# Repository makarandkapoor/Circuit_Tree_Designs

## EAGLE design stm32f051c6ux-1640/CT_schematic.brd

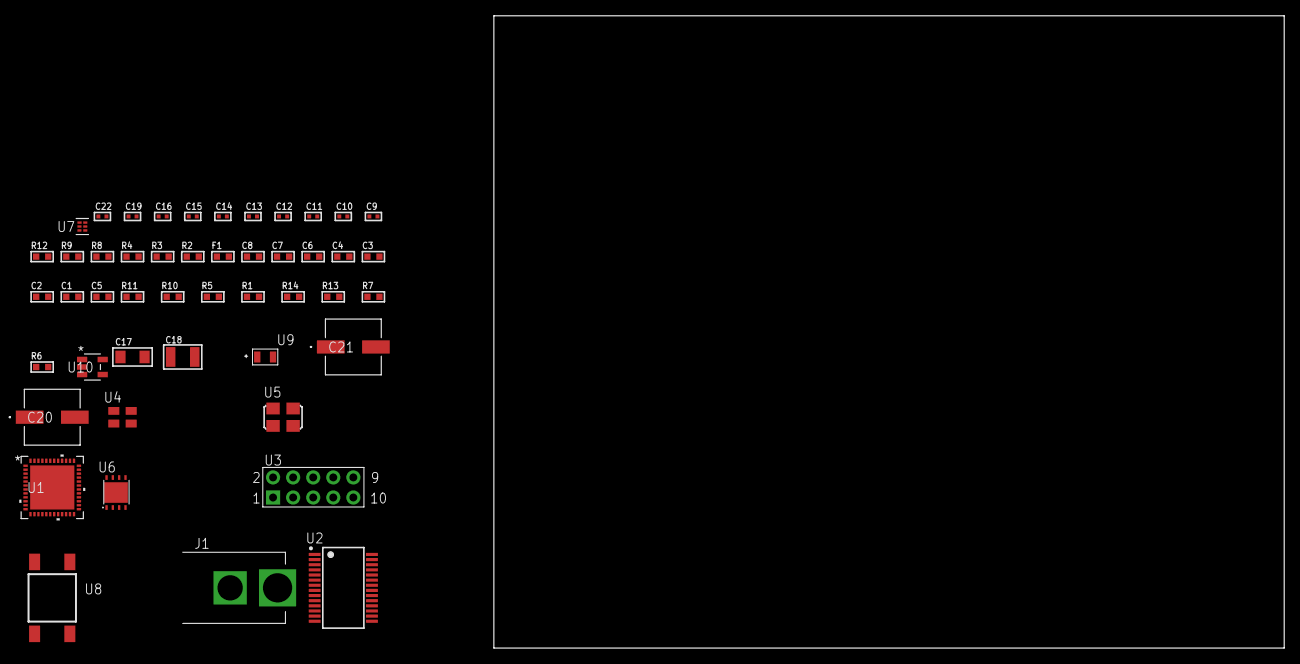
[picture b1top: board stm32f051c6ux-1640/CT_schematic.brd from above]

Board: 2 copper layers, 100.0 x 80.0 mm, 48 parts (0 on the bottom side), 32 nets, no tracks yet.

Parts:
C1, C8: 1e-06; C0603
C2, C3, C4, C6: 1e-07; C0603
C5: 4.7e-06; C0603
C7: 1e-08; C0603
C9, C10, C11, C12, C13, C19: 1e-07; C0402
C14, C15, C16, C22: 1e-08; C0402
C17: 1e-05; C1206
C18: 1e-05; C1210
C20, C21: 0.0001; EXV-9H
F1: 240.0; L0603
J1: PJ-037B; PJ-037B_PACKAGE
R1, R5, R10, R11: 10000.0; R0603
R2, R9: 1000.0; R0603
R3: 1600.5; R0603
R4: 4700.0; R0603
R6, R7: 100000.0; R0603
R8: 2231.0; R0603
R12: 9100.0; R0603
R13: 680000.0; R0603
R14: 120000.0; R0603
U1: stm32f051c6u6; UFQFPN48
U2: ST3241EBPR; SSOP-28
U3: HTSS-105-01-G-D
U4: ASEK-32.768KHz-ECST; ASEK
U5: ASFL1-25MHZ-NCS; ASFL1
U6: LP3878SDX-ADJ/NOPB; WSON-8
U7: TPS3895ADRYR; SON-6
U8: 4-1437565-2; SW_4-1437565-2
U9: Q65110A2395; LGM67K-G1J2-24-Z
U10: nc7sz125m5x; NC7SZ125M5X

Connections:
CLK_U1_3: U1.3, U4.3
CLK_U1_5: U1.5, U5.3
GND: C1.2, C2.2, C3.2, C4.2, C5.2, C6.2, C7.2, C8.2, C9.2, C12.2, C13.2, C14.2, C15.2, C16.2, C17.2, C18.2, C19.2, C20.2, C21.2, C22.2, J1.2, R2.2, R5.2, R9.2, R12.2, R14.2, U1.8, U1.23, U1.47, U1.49, U2.23, U2.25, U3.9, U4.2, U5.2, U6.3, U6.PAD, U7.2, U9.C, U10.1, U10.3
NET_U1_7: R4.1, U1.7, U10.4
NET_U1_9: C7.1, C8.1, F1.1, U1.9
NET_U1_44: R5.1, U1.44
NET_U1_45: R3.1, U1.45, U9.A
NET_U1_46: R1.1, U1.46, U8.3, U8.4
NET_U2_1: C11.1, U2.1
NET_U2_2: C11.2, U2.2
NET_U2_3: C13.1, U2.3
NET_U2_22: R6.1, U2.22
NET_U2_24: C10.2, U2.24
NET_U2_27: C12.1, U2.27
NET_U2_28: C10.1, U2.28
NET_U3_3: U2.4, U3.3
NET_U3_4: U2.5, U3.4
NET_U3_5: U2.9, U3.5
NET_U3_6: U2.10, U3.6
NET_U6_1: C16.1, U6.1
NET_U6_6: R8.2, R9.1, U6.6
NET_U6_8: R7.1, U6.8
NET_U7_1: R11.1, R12.1, U7.1
NET_U7_3: R13.2, R14.1, U7.3
NET_U7_4: R10.1, U7.4, U10.2
NET_U8_1: R2.1, U8.1, U8.2
PROC_USART1_CTS: U1.32, U2.13
PROC_USART1_RTS: U1.33, U2.18
PROC_USART1_RX: U1.31, U2.19
PROC_USART1_TX: U1.30, U2.14
VCC_S1_7V3: C17.1, C20.1, C21.1, J1.1, R7.2, U6.4
VCC_TIER1_3V3: C1.1, C2.1, C3.1, C4.1, C5.1, C6.1, C9.1, C14.1, C15.1, C18.1, C19.1, C22.1, F1.2, R1.2, R3.2, R4.2, R6.2, R8.1, R10.2, R11.2, R13.1, U1.1, U1.24, U1.48, U2.26, U4.4, U5.4, U6.5, U7.6, U10.5

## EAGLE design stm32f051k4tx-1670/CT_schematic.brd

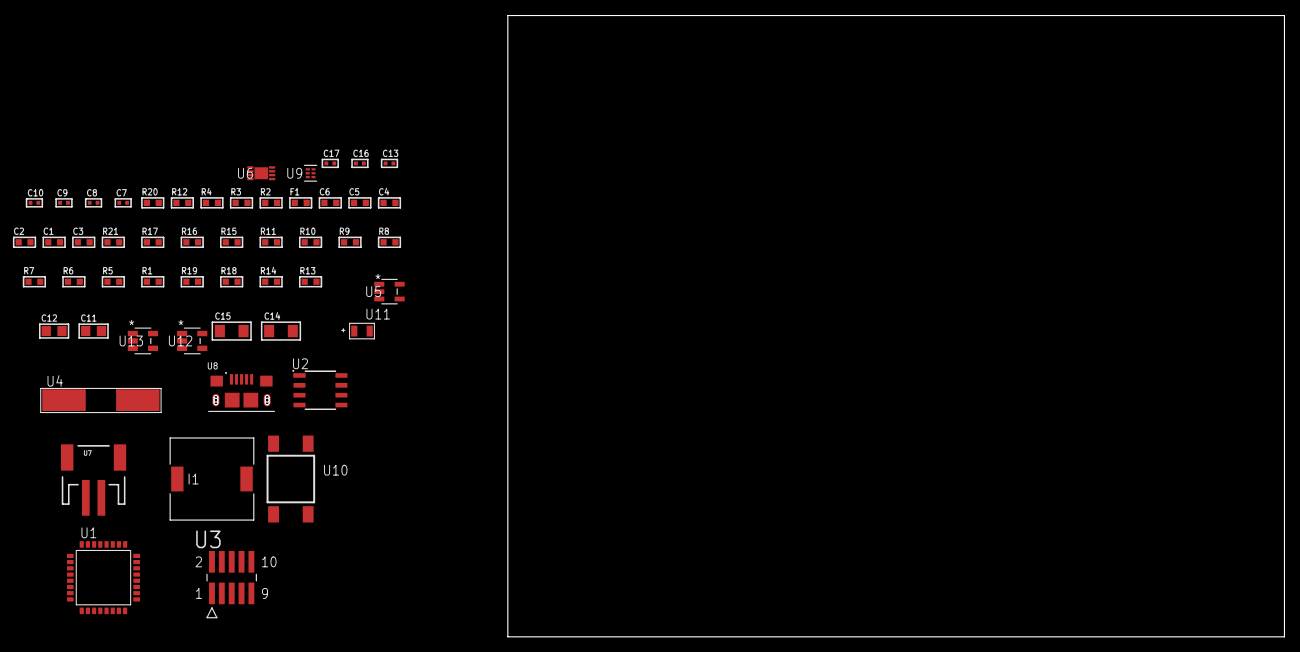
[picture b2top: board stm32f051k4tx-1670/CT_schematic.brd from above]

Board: 2 copper layers, 53 parts (0 on the bottom side), 30 nets, no tracks yet.

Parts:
C1, C2: 1e-07; C0603
C3: 4.7e-06; C0603
C4, C5: 1e-08; C0603
C6: 1e-06; C0603
C7, C8: 1e-11; C0402
C9, C16, C17: 1e-08; C0402
C10, C13: 1e-07; C0402
C11, C12: 1e-05; C0805
C14, C15: 1e-05; C1206
F1: 240.0; L0603
I1: 7e-06; DR1040
R1, R5, R6, R7, R8, R9, R10, R11, R15, R16, R21: 10000.0; R0603
R2: 1000.0; R0603
R3: 1270.0; R0603
R4: 4700.0; R0603
R12: 5.0; R0603
R13: 309473.68421053; R0603
R14: 1000000.0; R0603
R17: 18000.0; R0603
R18: 470000.0; R0603
R19: 120000.0; R0603
R20: 2000.0; R0603
U1: stm32f051k4t7; LQFP32
U2: AT25010B-SSHL-T; SOIC-8
U3: FTSH-105-01-L-DV-K; SAMTEC_FTSH-105-01-L-DV-K
U4: ABLS-25.000MHZ-B2F-T
U5: ltc3406es5; TSOT-23-5
U6: MCP73831T-2ACI/MC; DFN8_2X3MC
U7: S2B-PH-SM4-TB(LF)(SN); JST-2-SMD
U8: 10118193-0001LF; FCI_10118193-0001LF
U9: TPS3895ADRYR; SON-6
U10: 4-1437565-2; SW_4-1437565-2
U11: Q65110A2395; LGM67K-G1J2-24-Z
U12, U13: nc7sz125m5x; NC7SZ125M5X

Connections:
CLK_CRYSTAL_U1_2: C7.1, U1.2, U4.1
CLK_CRYSTAL_U1_3: C8.1, U1.3, U4.2
GND: C1.2, C2.2, C3.2, C4.2, C5.2, C6.2, C7.2, C8.2, C9.2, C10.2, C11.2, C12.1, C12.2, C13.2, C14.2, C15.2, C16.2, C17.2, R2.2, R5.2, R12.2, R13.2, R17.2, R19.2, R20.2, U1.16, U1.32, U2.4, U3.3, U3.5, U5.2, U6.6, U6.9, U7.2, U8.5, U8.6, U8.7, U8.8, U8.9, U9.2, U11.C, U12.2, U12.3, U13.1, U13.3
INPUT_USBPOWER_5V: C14.1, R21.2, U6.1, U6.2, U8.1
NET_U1_4: R4.1, U1.4, U13.4
NET_U1_5: C4.1, C5.1, C6.1, F1.1, U1.5
NET_U1_29: R3.1, U1.29, U11.A
NET_U1_30: R1.1, U1.30, U10.3, U10.4
NET_U1_31: R5.1, U1.31
NET_U2_3: R6.1, U2.3
NET_U2_7: R8.1, U2.7
NET_U3_4: R10.1, U3.4
NET_U3_9: R12.1, U3.9
NET_U5_3: I1.1, U5.3
NET_U5_5: R13.1, R14.1, U5.5
NET_U5_ATNET_3: I1.2, R14.2
NET_U6_5: R21.1, U6.5
NET_U6_8: R20.1, U6.8
NET_U9_1: R16.1, R17.1, U9.1
NET_U9_3: R18.2, R19.1, U9.3
NET_U9_4: R15.1, U9.4, U12.4, U13.2
NET_U10_1: R2.1, U10.1, U10.2
PROC_SPI1_MISO: U1.12, U2.2
PROC_SPI1_MOSI: U1.13, U2.5
PROC_SPI1_NSS: R7.1, U1.10, U2.1
PROC_SPI1_SCK: U1.11, U2.6
PROC_SYS_SWDIO: R11.1, U1.23, U3.2
RST_OUT_U3_JTAG_RST_B: R9.1, U3.10, U12.1
VCC_S1_3V7: C11.1, C15.1, U5.4, U6.3, U6.4, U7.1
VCC_TIER1_2V5: C1.1, C2.1, C3.1, C9.1, C10.1, C12.2, C13.1, C16.1, C17.1, F1.2, I1.2, R1.2, R3.2, R4.2, R6.2, R7.2, R8.2, R9.2, R10.2, R11.2, R14.2, R15.2, R16.2, R18.1, U1.1, U1.17, U2.8, U3.1, U9.6, U12.5, U13.5

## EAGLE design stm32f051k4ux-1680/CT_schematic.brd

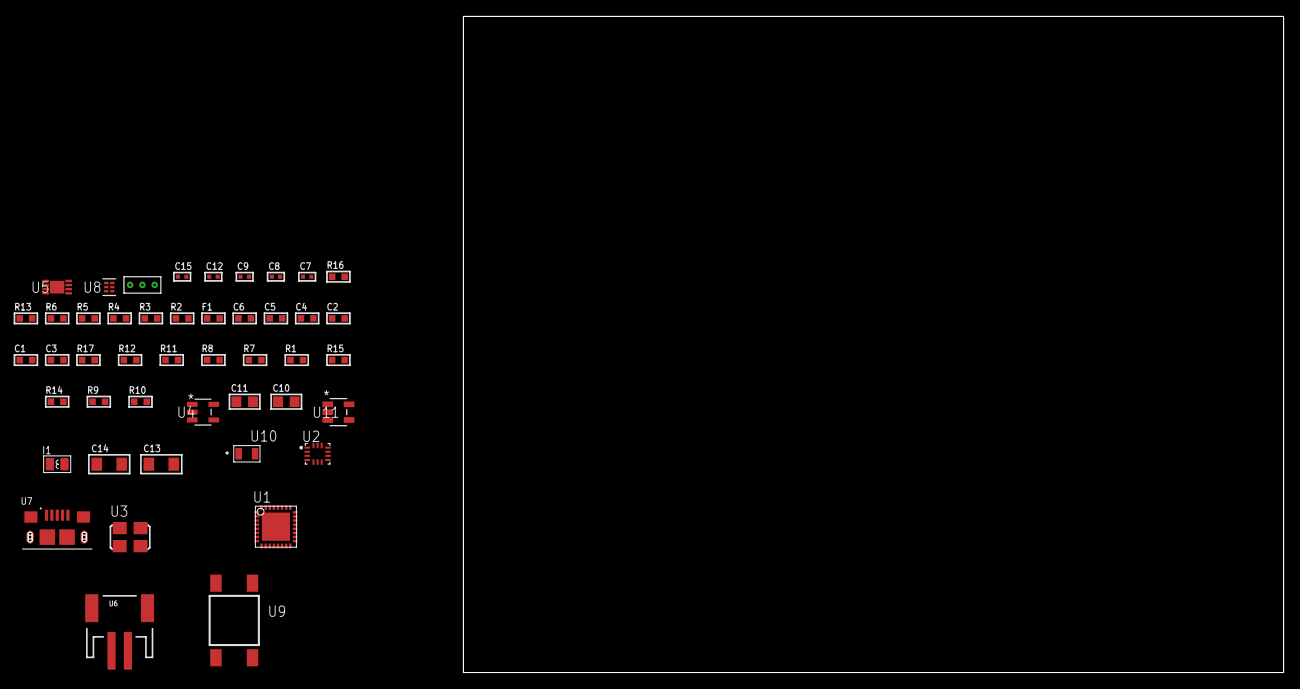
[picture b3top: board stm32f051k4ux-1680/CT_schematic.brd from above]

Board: 2 copper layers, 153.1 x 80.0 mm, 46 parts (0 on the bottom side), 25 nets, no tracks yet.

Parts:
C1, C2: 1e-07; C0603
C3: 4.7e-06; C0603
C4, C5: 1e-08; C0603
C6: 1e-06; C0603
C7, C8, C12: 1e-07; C0402
C9, C15: 1e-08; C0402
C10, C11: 1e-05; C0805
C13, C14: 1e-05; C1206
F1: 240.0; L0603
I1: 3.3e-06; L0806
R1, R7, R8, R11, R12, R17: 10000.0; R0603
R2: 1000.0; R0603
R3: 1600.5; R0603
R4: 4700.0; R0603
R5, R6: 2200.0; R0603
R9: 220000.0; R0603
R10: 1000000.0; R0603
R13: 9100.0; R0603
R14: 680000.0; R0603
R15: 120000.0; R0603
R16: 2000.0; R0603
U1: stm32f051k4u7; UFQFPN32
U2: BMG250; LGA-14
U3: ASFL1-25MHZ-NCS; ASFL1
U4: ltc3406es5; TSOT-23-5
U5: MCP73831T-2ACI/MC; DFN8_2X3MC
U6: S2B-PH-SM4-TB(LF)(SN); JST-2-SMD
U7: 10118193-0001LF; FCI_10118193-0001LF
U8: TPS3895ADRYR; SON-6
U9: 4-1437565-2; SW_4-1437565-2
U10: Q65110A2395; LGM67K-G1J2-24-Z
U11: nc7sz125m5x; NC7SZ125M5X
U12: Dummy; DUMMY_PACKAGE_99

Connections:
CLK_U1_2: U1.2, U3.3
GND: C1.2, C2.2, C3.2, C4.2, C5.2, C6.2, C7.2, C8.2, C9.2, C10.2, C11.1, C11.2, C12.2, C13.2, C14.2, C15.2, R2.2, R7.2, R9.2, R13.2, R15.2, R16.2, U1.EPAD, U2.1, U2.6, U2.7, U3.2, U4.2, U5.6, U5.9, U6.2, U7.5, U7.6, U7.7, U7.8, U7.9, U8.2, U10.C, U11.1, U11.3, U12.1
INPUT_USBPOWER_5V: C13.1, R17.2, U5.1, U5.2, U7.1
NET_U1_4: R4.1, U1.4, U11.4
NET_U1_5: C4.1, C5.1, C6.1, F1.1, U1.5
NET_U1_28: R3.1, U1.28, U10.A
NET_U1_29: R5.1, U1.29, U2.13
NET_U1_30: R6.1, U1.30, U2.14
NET_U1_31: R7.1, U1.31
NET_U1_32: R1.1, U1.32, U9.3, U9.4
NET_U2_12: R8.1, U2.12
NET_U4_3: I1.1, U4.3
NET_U4_5: R9.1, R10.1, U4.5
NET_U4_ATNET_3: I1.2, R10.2
NET_U5_5: R17.1, U5.5
NET_U5_8: R16.1, U5.8
NET_U8_1: R12.1, R13.1, U8.1
NET_U8_3: R14.2, R15.1, U8.3
NET_U8_4: R11.1, U8.4, U11.2
NET_U9_1: R2.1, U9.1, U9.2
PROC_GPIO_TO_U2_INT1: U1.3, U2.4
PROC_PA0: U1.6, U12.2
PROC_PA1: U1.7, U12.3
VCC_S1_3V7: C10.1, C14.1, U4.4, U5.3, U5.4, U6.1
VCC_TIER1_3V3: C1.1, C2.1, C3.1, C7.1, C8.1, C9.1, C11.2, C12.1, C15.1, F1.2, I1.2, R1.2, R3.2, R4.2, R5.2, R6.2, R8.2, R10.2, R11.2, R12.2, R14.1, U1.1, U1.17, U2.5, U2.8, U3.4, U8.6, U11.5

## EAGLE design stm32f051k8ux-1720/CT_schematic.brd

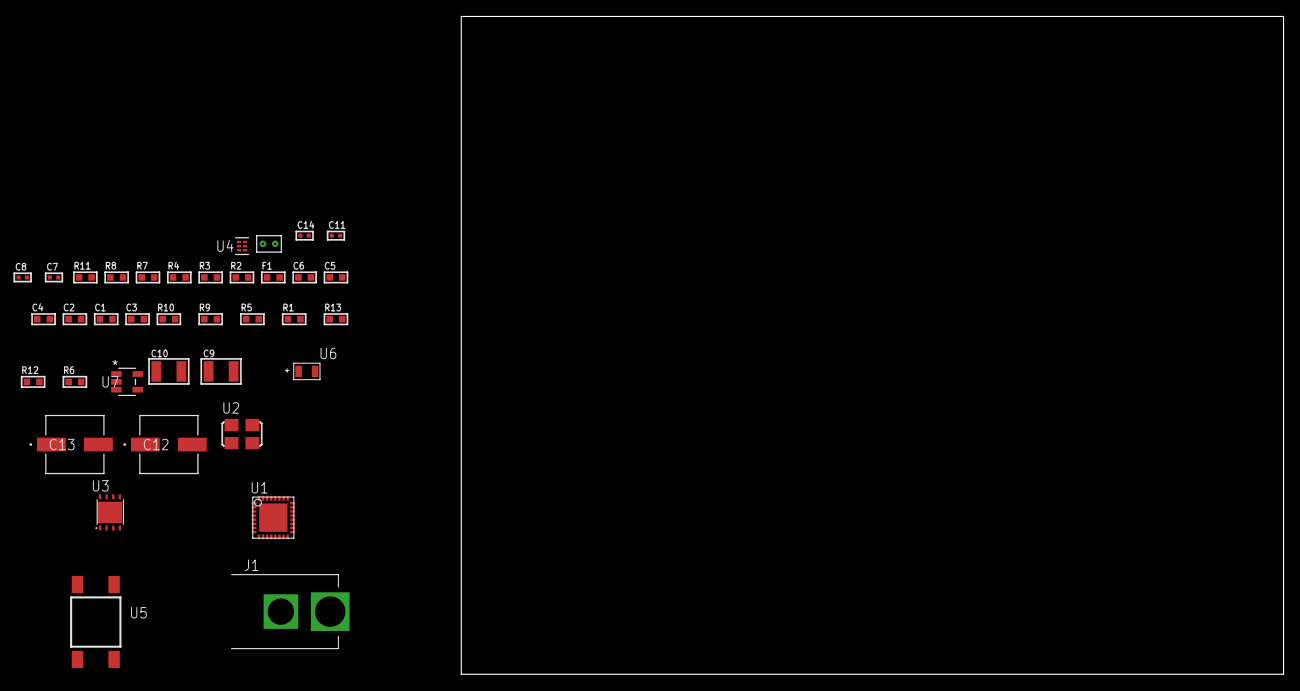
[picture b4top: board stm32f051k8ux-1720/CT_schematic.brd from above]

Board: 2 copper layers, 100.0 x 80.0 mm, 37 parts (0 on the bottom side), 17 nets, no tracks yet.

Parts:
C1, C2: 1e-07; C0603
C3: 4.7e-06; C0603
C4, C5: 1e-08; C0603
C6: 1e-06; C0603
C7, C8, C14: 1e-08; C0402
C9, C10: 1e-05; C1210
C11: 1e-07; C0402
C12, C13: 0.0001; EXV-9H
F1: 240.0; L0603
J1: PJ-037B; PJ-037B_PACKAGE
R1, R5, R9, R10: 10000.0; R0603
R2, R8: 1000.0; R0603
R3: 1600.5; R0603
R4: 4700.0; R0603
R6: 100000.0; R0603
R7: 2231.0; R0603
R11: 9100.0; R0603
R12: 680000.0; R0603
R13: 120000.0; R0603
U1: stm32f051k8u7; UFQFPN32
U2: ASFL1-25MHZ-NCS; ASFL1
U3: LP3878SDX-ADJ/NOPB; WSON-8
U4: TPS3895ADRYR; SON-6
U5: 4-1437565-2; SW_4-1437565-2
U6: Q65110A2395; LGM67K-G1J2-24-Z
U7: nc7sz125m5x; NC7SZ125M5X
U8: Dummy; DUMMY_PACKAGE_74

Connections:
CLK_U1_2: U1.2, U2.3
GND: C1.2, C2.2, C3.2, C4.2, C5.2, C6.2, C7.2, C8.2, C9.2, C10.2, C11.2, C12.2, C13.2, C14.2, J1.2, R2.2, R5.2, R8.2, R11.2, R13.2, U1.EPAD, U2.2, U3.3, U3.PAD, U4.2, U6.C, U7.1, U7.3, U8.1
NET_U1_4: R4.1, U1.4, U7.4
NET_U1_5: C4.1, C5.1, C6.1, F1.1, U1.5
NET_U1_30: R3.1, U1.30, U6.A
NET_U1_31: R5.1, U1.31
NET_U1_32: R1.1, U1.32, U5.3, U5.4
NET_U3_1: C8.1, U3.1
NET_U3_6: R7.2, R8.1, U3.6
NET_U3_8: R6.1, U3.8
NET_U4_1: R10.1, R11.1, U4.1
NET_U4_3: R12.2, R13.1, U4.3
NET_U4_4: R9.1, U4.4, U7.2
NET_U5_1: R2.1, U5.1, U5.2
PROC_DAC1_OUT1: U1.10, U8.2
VCC_S1_11V9: C9.1, C12.1, C13.1, J1.1, R6.2, U3.4
VCC_TIER1_3V3: C1.1, C2.1, C3.1, C7.1, C10.1, C11.1, C14.1, F1.2, R1.2, R3.2, R4.2, R7.1, R9.2, R10.2, R12.1, U1.1, U1.17, U2.4, U3.5, U4.6, U7.5

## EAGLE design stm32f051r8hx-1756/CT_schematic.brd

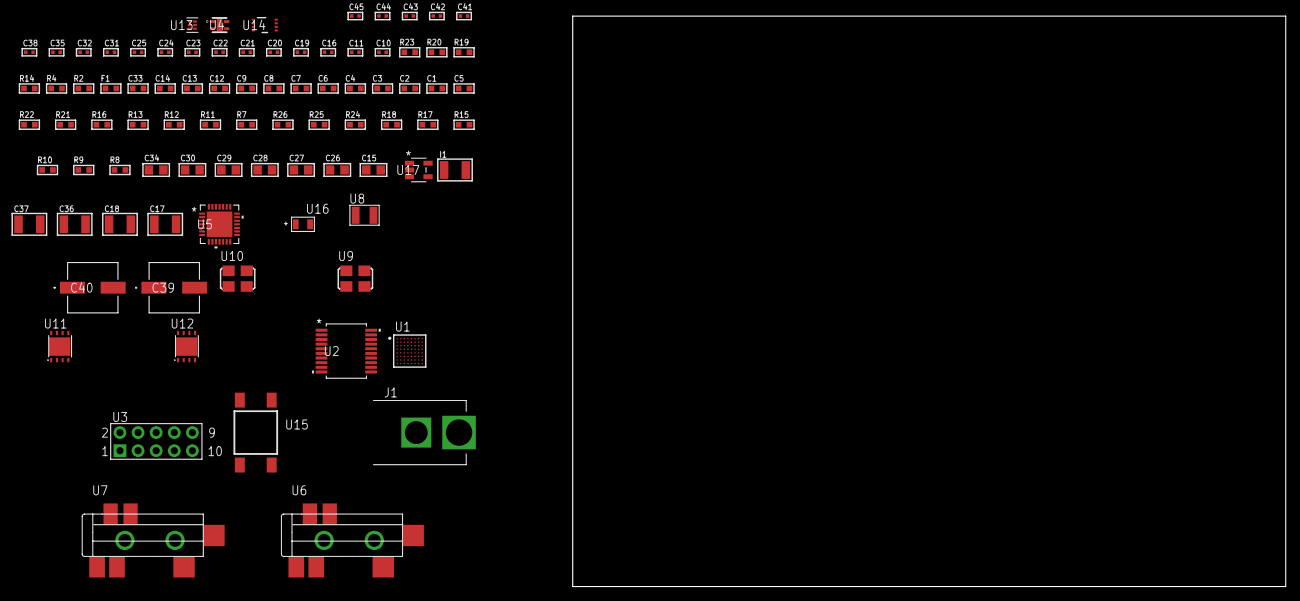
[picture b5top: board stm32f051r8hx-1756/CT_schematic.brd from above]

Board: 2 copper layers, 100.0 x 80.0 mm, 87 parts (0 on the bottom side), 47 nets, no tracks yet.

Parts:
C1, C9, C12, C13, C14: 1e-06; C0603
C2, C3, C4, C6, C7: 1e-07; C0603
C5: 4.7e-06; C0603
C8: 1e-08; C0603
C10, C11: 1e-11; C0402
C15: 4.7e-06; C0805
C16, C21, C22, C23, C24, C25, C38, C42, C44: 1e-07; C0402
C17, C18: 2.2e-05; C1210
C19, C20: 1e-09; C0402
C26, C27, C28, C29, C30, C34: 1e-05; C0805
C31, C32, C35, C41, C43, C45: 1e-08; C0402
C33: 8e-07; R0603
C36, C37: 1e-05; C1210
C39, C40: 0.0001; EXV-9H
F1: 240.0; L0603
I1: 1.5e-05; L1210
J1: PJ-037B; PJ-037B_PACKAGE
R2, R20: 1000.0; R0603
R4: 4700.0; R0603
R7, R21, R22: 10000.0; R0603
R8, R9, R10, R15, R17, R18: 100000.0; R0603
R11, R12, R13: 47000.0; R0603
R14: 680.0; R0603
R16: 36000.0; R0603
R19: 2231.0; R0603
R23: 9100.0; R0603
R24: 680000.0; R0603
R25: 120000.0; R0603
R26: 200000.0; R0603
U1: stm32f051r8h7; UFBGA64
U2: MAX3218EAP+T; SSOP-20
U3: HTSS-105-01-G-D
U4: Si7034-A10-IM; SI7034-A10-IM
U5: WM8731CLSEFL; QFN-28
U6, U7: SJ-43515TS-SMT-TR
U8: ABS07-32.768KHZ-7-T
U9: ASFL1-12.288MHZ-EC-T; ASFL1
U10: ASFL1-25MHZ-NCS; ASFL1
U11: LP2951ACSDX/NOPB; WSON-8
U12: LP3878SDX-ADJ/NOPB; WSON-8
U13: TPS3895ADRYR; SON-6
U14: LSF0102DCTR; DCU0008A_N
U15: 4-1437565-2; SW_4-1437565-2
U16: Q65110A2395; LGM67K-G1J2-24-Z
U17: nc7sz125m5x; NC7SZ125M5X

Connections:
CLK_CRYSTAL_U1_A1: C10.1, U1.A1, U8.1
CLK_CRYSTAL_U1_B1: C11.1, U1.B1, U8.2
CLK_U1_C1: U1.C1, U10.3
CLK_U5_1: U5.1, U9.3
GND: C1.2, C2.2, C3.2, C4.2, C5.2, C6.2, C7.2, C8.2, C9.2, C10.2, C11.2, C12.2, C13.2, C14.2, C16.2, C20.2, C21.2, C22.2, C23.2, C24.2, C25.2, C26.2, C27.2, C28.2, C29.2, C30.2, C31.2, C32.2, C33.2, C34.2, C35.2, C36.2, C37.2, C38.2, C39.2, C40.2, C41.2, C42.2, C43.2, C44.2, C45.2, J1.2, R2.2, R7.2, R11.2, R12.2, R13.2, R17.2, R20.2, R23.2, R25.2, U1.D4, U1.D5, U1.F1, U2.5, U2.17, U2.20, U3.9, U4.5, U5.4, U5.15, U5.19, U5.25, U5.26, U5.29, U6.1, U7.1, U9.2, U10.2, U11.3, U11.4, U11.PAD, U12.3, U12.PAD, U13.2, U14.1, U16.C, U17.1, U17.3
NET_U1_B4: R7.1, U1.B4
NET_U1_E1: R4.1, U1.E1, U17.4
NET_U1_H1: C8.1, C9.1, F1.1, U1.H1
NET_U1_H8: U15.3, U15.4
NET_U2_1: I1.1, U2.1
NET_U2_2: R8.1, U2.2
NET_U2_3: R9.1, U2.3
NET_U2_4: R10.1, U2.4
NET_U2_15: C14.1, U2.15
NET_U2_16: C15.2, U2.16
NET_U2_18: C15.1, U2.18
NET_U2_19: C13.1, U2.19
NET_U3_3: U2.12, U3.3
NET_U3_4: U2.11, U3.4
NET_U3_5: U2.14, U3.5
NET_U3_6: U2.13, U3.6
NET_U5_20: C25.1, C30.1, U5.20
NET_U6_2: C18.1, R12.1, U6.2
NET_U6_5: C17.1, R11.1, U6.5
NET_U7_5: C19.1, C20.1, R13.1, R14.1, U7.5
NET_U11_5: R15.1, U11.5
NET_U11_7: R16.2, R17.1, U11.7
NET_U12_1: C35.1, U12.1
NET_U12_6: R19.2, R20.1, U12.6
NET_U12_8: R18.1, U12.8
NET_U13_1: R22.1, R23.1, U13.1
NET_U13_3: R24.2, R25.1, U13.3
NET_U13_4: R21.1, U13.4, U17.2
NET_U14_8: R26.1, U14.8
NET_U15_1: R2.1, U15.1, U15.2
PROC_I2C1_SCL_TOXCVR: U4.2, U14.5
PROC_I2C1_SDA_TOXCVR: U4.4, U14.6
PROC_I2S1_CK: U1.A5, U5.7
PROC_I2S1_SD: U1.C4, U5.8
PROC_I2S1_WS: U1.A6, U5.9, U5.11
PROC_USART1_CTS: U1.C8, U2.8
PROC_USART1_RTS: U1.B8, U2.10
PROC_USART1_RX: U1.C3, U2.9
PROC_USART1_TX: U1.C7, U2.7
VCC_S1_11V7: C33.1, C36.1, C39.1, C40.1, J1.1, R18.2, U11.8, U12.4
VCC_TIER1_1V8: C16.1, C21.1, C23.1, C24.1, C26.1, C28.1, C29.1, C34.1, C41.1, C42.1, C45.1, R15.2, R16.1, R26.2, U4.1, U5.5, U5.12, U5.18, U11.1, U14.7, U17.5
VCC_TIER1_3V3: C1.1, C2.1, C3.1, C4.1, C5.1, C6.1, C7.1, C12.1, C22.1, C27.1, C31.1, C32.1, C37.1, C38.1, C43.1, C44.1, F1.2, I1.2, R4.2, R8.2, R9.2, R10.2, R19.1, R21.2, R22.2, R24.1, U1.B2, U1.E4, U1.E5, U2.6, U5.3, U9.4, U10.4, U12.5, U13.6, U14.2

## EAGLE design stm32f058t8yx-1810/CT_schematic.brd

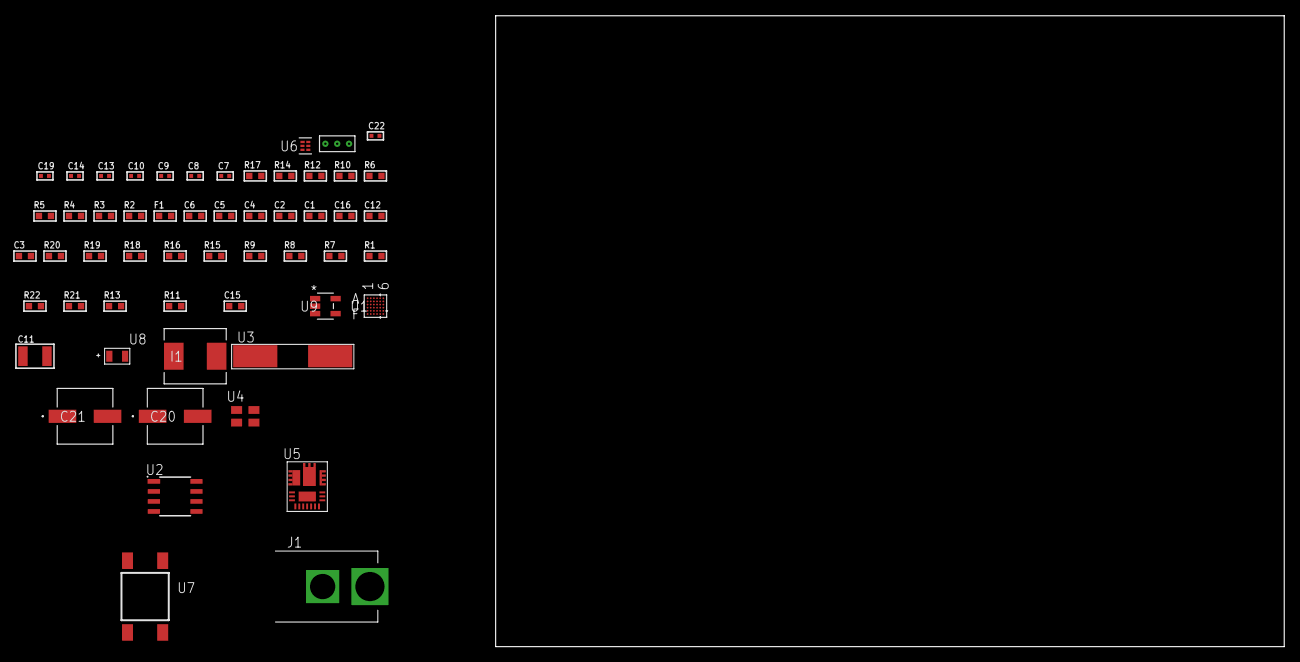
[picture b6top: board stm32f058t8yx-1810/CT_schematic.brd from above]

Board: 2 copper layers, 100.0 x 80.0 mm, 55 parts (0 on the bottom side), 31 nets, no tracks yet.

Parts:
C1, C2: 1e-07; C0603
C3: 4.7e-06; C0603
C4, C5: 1e-08; C0603
C6: 1e-06; C0603
C7, C8: 1e-11; C0402
C9, C10, C22: 1e-08; C0402
C11: 0.0001; C1210
C12: 2.2e-06; C0603
C13, C14, C19: 1e-07; C0402
C15: 7.8444498006919e-09; R0603
C16: 2.7e-07; C0603
C20, C21: 0.0001; EXV-9H
F1: 240.0; L0603
I1: 6.8e-07; IND25X25CZ
J1: PJ-037B; PJ-037B_PACKAGE
R1, R7, R8, R9, R18, R19: 10000.0; R0603
R2: 1000.0; R0603
R3: 910.0; R0603
R4: 4700.0; R0603
R5, R6: 2200.0; R0603
R10: 0.1; R0603
R11: 4030.2416170974; R0603
R12: 1600.0; R0603
R13: 64.984347826087; R0603
R14: 130.0; R0603
R15: 39000.0; R0603
R16: 49900.0; R0603
R17: 5600.0; R0603
R20: 82000.0; R0603
R21: 300000.0; R0603
R22: 120000.0; R0603
U1: stm32f058t8y6; WLCSP36
U2: M24M02-DRMN6TP; SOIC-8
U3: ABLS-25.000MHZ-B2F-T
U4: ASEK-2-32.768KHz-ECST; ASEK
U5: IR3899MTR1PBF
U6: TPS3895ADRYR; SON-6
U7: 4-1437565-2; SW_4-1437565-2
U8: Q65110A2395; LGM67K-G1J2-24-Z
U9: nc7sz125m5x; NC7SZ125M5X
U10: Dummy; DUMMY_PACKAGE_104

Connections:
CLK_CRYSTAL_U1_B5: C7.1, U1.B5, U3.1
CLK_CRYSTAL_U1_C5: C8.1, U1.C5, U3.2
CLK_U1_B6: U1.B6, U4.3
GND: C1.2, C2.2, C3.2, C4.2, C5.2, C6.2, C7.2, C8.2, C9.2, C10.2, C12.2, C13.2, C14.2, C19.2, C20.2, C21.2, C22.2, J1.2, R2.2, R7.2, R8.2, R9.2, R10.1, R10.2, R12.2, R15.2, R17.2, R20.2, R22.2, U1.D6, U1.F1, U2.4, U4.2, U5.4, U5.11, U5.17, U6.2, U8.C, U9.1, U9.3, U10.1
NET_U1_A4: R6.1, U1.A4, U2.5
NET_U1_B4: R7.1, U1.B4
NET_U1_C4: R5.1, U1.C4, U2.6
NET_U1_D5: R4.1, U1.D5, U9.4
NET_U1_E5: C4.1, C5.1, C6.1, F1.1, U1.E5
NET_U1_F2: R8.1, U1.F2
NET_U1_F5: R3.1, U1.F5, U8.A
NET_U1_F6: R1.1, U1.F6, U7.3, U7.4
NET_U2_3: R9.1, U2.3
NET_U5_1: C15.1, R11.1, R12.1, R13.1, R14.1, U5.1, U5.8
NET_U5_2: C14.1, U5.2
NET_U5_3: C15.2, C16.1, C16.2, U5.3
NET_U5_5: R15.1, U5.5
NET_U5_10: C12.1, U5.10
NET_U5_12: C11.1, I1.1, U5.12
NET_U5_14: C11.2, U5.14
NET_U5_15: R16.1, R17.1, U5.15
NET_U5_ATNET_3: I1.2, R11.2
NET_U5_ATNET_4: C16.2, R13.2
NET_U6_1: R19.1, R20.1, U6.1
NET_U6_3: R21.2, R22.1, U6.3
NET_U6_4: R18.1, U6.4, U9.2
NET_U7_1: R2.1, U7.1, U7.2
PROC_PA12: U1.A1, U10.2
PROC_PA15: U1.A2, U10.3
VCC_S1_16V1: C13.1, C20.1, C21.1, J1.1, R16.2, U5.9
VCC_TIER1_1V8: C1.1, C2.1, C3.1, C9.1, C10.1, C19.1, C22.1, F1.2, I1.2, R1.2, R3.2, R4.2, R5.2, R6.2, R11.2, R18.2, R19.2, R21.1, U1.A5, U1.E1, U2.8, U4.4, U6.6, U9.5

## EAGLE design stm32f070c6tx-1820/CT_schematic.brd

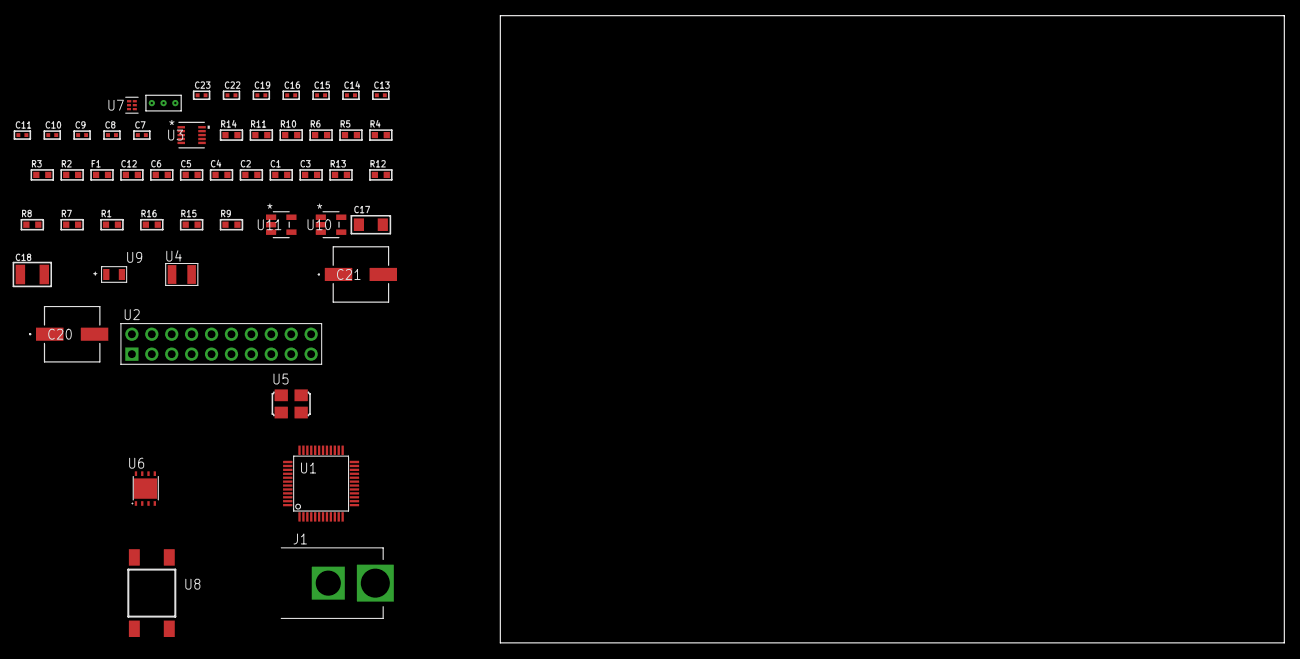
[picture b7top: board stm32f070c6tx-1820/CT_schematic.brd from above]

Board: 2 copper layers, 100.0 x 80.0 mm, 53 parts (0 on the bottom side), 27 nets, no tracks yet.

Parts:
C1, C2, C4: 1e-07; C0603
C3: 4.7e-06; C0603
C5: 1e-08; C0603
C6, C12: 1e-06; C0603
C7, C8: 1e-11; C0402
C9, C10, C11, C13, C14, C19: 1e-07; C0402
C15, C16, C22, C23: 1e-08; C0402
C17: 1e-05; C1206
C18: 1e-05; C1210
C20, C21: 0.0001; EXV-9H
F1: 240.0; L0603
J1: PJ-037B; PJ-037B_PACKAGE
R1, R7, R8, R12, R13: 10000.0; R0603
R2, R11: 1000.0; R0603
R3: 1600.5; R0603
R4: 4700.0; R0603
R5, R6: 2200.0; R0603
R9: 100000.0; R0603
R10: 2231.0; R0603
R14: 9100.0; R0603
R15: 680000.0; R0603
R16: 120000.0; R0603
U1: stm32f070c6t7; LQFP48
U2: TST-110-05-T-D-RA
U3: MAG3110FCR1; DFN-10
U4: ABS07-32.768KHZ-7-T
U5: ASFL1-25MHZ-NCS; ASFL1
U6: LP3878SDX-ADJ/NOPB; WSON-8
U7: TPS3895ADRYR; SON-6
U8: 4-1437565-2; SW_4-1437565-2
U9: Q65110A2395; LGM67K-G1J2-24-Z
U10, U11: nc7sz125m5x; NC7SZ125M5X
U12: Dummy; DUMMY_PACKAGE_110

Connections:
CLK_CRYSTAL_U1_3: C7.1, U1.3, U4.1
CLK_CRYSTAL_U1_4: C8.1, U1.4, U4.2
CLK_U1_5: U1.5, U5.3
GND: C1.2, C2.2, C3.2, C4.2, C5.2, C6.2, C7.2, C8.2, C9.2, C10.2, C11.2, C12.2, C13.2, C14.2, C15.2, C16.2, C17.2, C18.2, C19.2, C20.2, C21.2, C22.2, C23.2, J1.2, R2.2, R7.2, R11.2, R14.2, R16.2, U1.8, U1.23, U1.35, U1.47, U2.4, U2.6, U2.8, U2.10, U2.12, U2.14, U2.16, U2.18, U2.20, U3.5, U3.10, U5.2, U6.3, U6.PAD, U7.2, U9.C, U10.2, U10.3, U11.1, U11.3, U12.1
NET_U1_6: R5.1, U1.6, U3.7
NET_U1_7: R4.1, U1.7, U11.4
NET_U1_9: C5.1, C6.1, F1.1, U1.9
NET_U1_31: R6.1, U1.31, U3.6
NET_U1_44: R7.1, U1.44
NET_U1_45: R3.1, U1.45, U9.A
NET_U1_46: R1.1, U1.46, U8.3, U8.4
NET_U3_1: C10.1, U3.1
NET_U3_4: C13.1, U3.4
NET_U6_1: C16.1, U6.1
NET_U6_6: R10.2, R11.1, U6.6
NET_U6_8: R9.1, U6.8
NET_U7_1: R13.1, R14.1, U7.1
NET_U7_3: R15.2, R16.1, U7.3
NET_U7_4: R12.1, U7.4, U10.4, U11.2
NET_U8_1: R2.1, U8.1, U8.2
PROC_SYS_SWCLK: U1.37, U2.9
PROC_SYS_SWDIO: U1.34, U2.7
PROC_TIM1_CH3N: U1.19, U12.3
PROC_TIM1_CH4: U1.32, U12.2
RST_OUT_U2_SRESET_B: R8.1, U2.15, U10.1
VCC_S1_5V9: C17.1, C20.1, C21.1, J1.1, R9.2, U6.4
VCC_TIER1_3V3: C1.1, C2.1, C3.1, C4.1, C9.1, C11.1, C12.1, C14.1, C15.1, C18.1, C19.1, C22.1, C23.1, F1.2, R1.2, R3.2, R4.2, R5.2, R6.2, R8.2, R10.1, R12.2, R13.2, R15.1, U1.1, U1.24, U1.36, U1.48, U2.1, U3.2, U3.8, U5.4, U6.5, U7.6, U10.5, U11.5
